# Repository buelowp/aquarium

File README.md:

# Aquarium Sensor Monitor

I have had aquariums for a while, so I decided one day to add some specific sensors to help me keep track of the
health of the aquarium over time. Atlas makes some really nice, if not expensive, water sensors than can be used in both
fresh and saltwater tanks. For my freshwater tank, I plan to add dissolved oxygen and a pH sensor to help me keep track
of what's going on during the day. I also plan to add a temperature monitor and have added support for keeping track 
of the flow rate for the pump and a water level sensor to make sure I have water in there. The goal is to give me 
some insight into tank health as time goes by, and provide me with rapid warning if something critically bad happens.

To do this, I've created a board to hold a Rasperry PI Zero W, along with space to add the Atlas sensors and a ADC to 
help me keep track of water level. It is a somewhat complicated 4 layer PCB that includes the PI, three Atlas sensor installations, two temp probes, a couple of random GPIO (to control whatever), and an 8 channel ADC, though currently 
I only use 1. They don't make a through hole 1 channel ADC that I can find.

This is also designed to work with my Android Things Aquarium display, which will give me some visual feedback when 
wanted about the state of the tank. It will also give me the ability to track cleanings, filter changes, and a list 
of other things that should be tracked over time to avoid letting them go too long.

## Installation

You need a PI zero, with build-essentials and cmake. You compile it doing the following

```
mkdir build
cd build
cmake ..
make
cp app/aquarium /usr/bin
```

You must copy the aquarium.config file to /root/.config, as this app MUST run as root. It's easiest if you start 
it from rc.local as the last item in the list. It has a function to wait on the network, so that shouldn't be too 
big a problem. If the MQTT server doesn't come up in 5 minutes, it will fail. The whole point of this is MQTT 
access to data. It also can talk to AdafruitIO, but doesn't block waiting for that. If that doesn't connect, then 
you can't talk to AdafruitIO.

I won't got into detail about how to build out the hardware right now.

## Configuration

I will describe how to populate the config file here soon.

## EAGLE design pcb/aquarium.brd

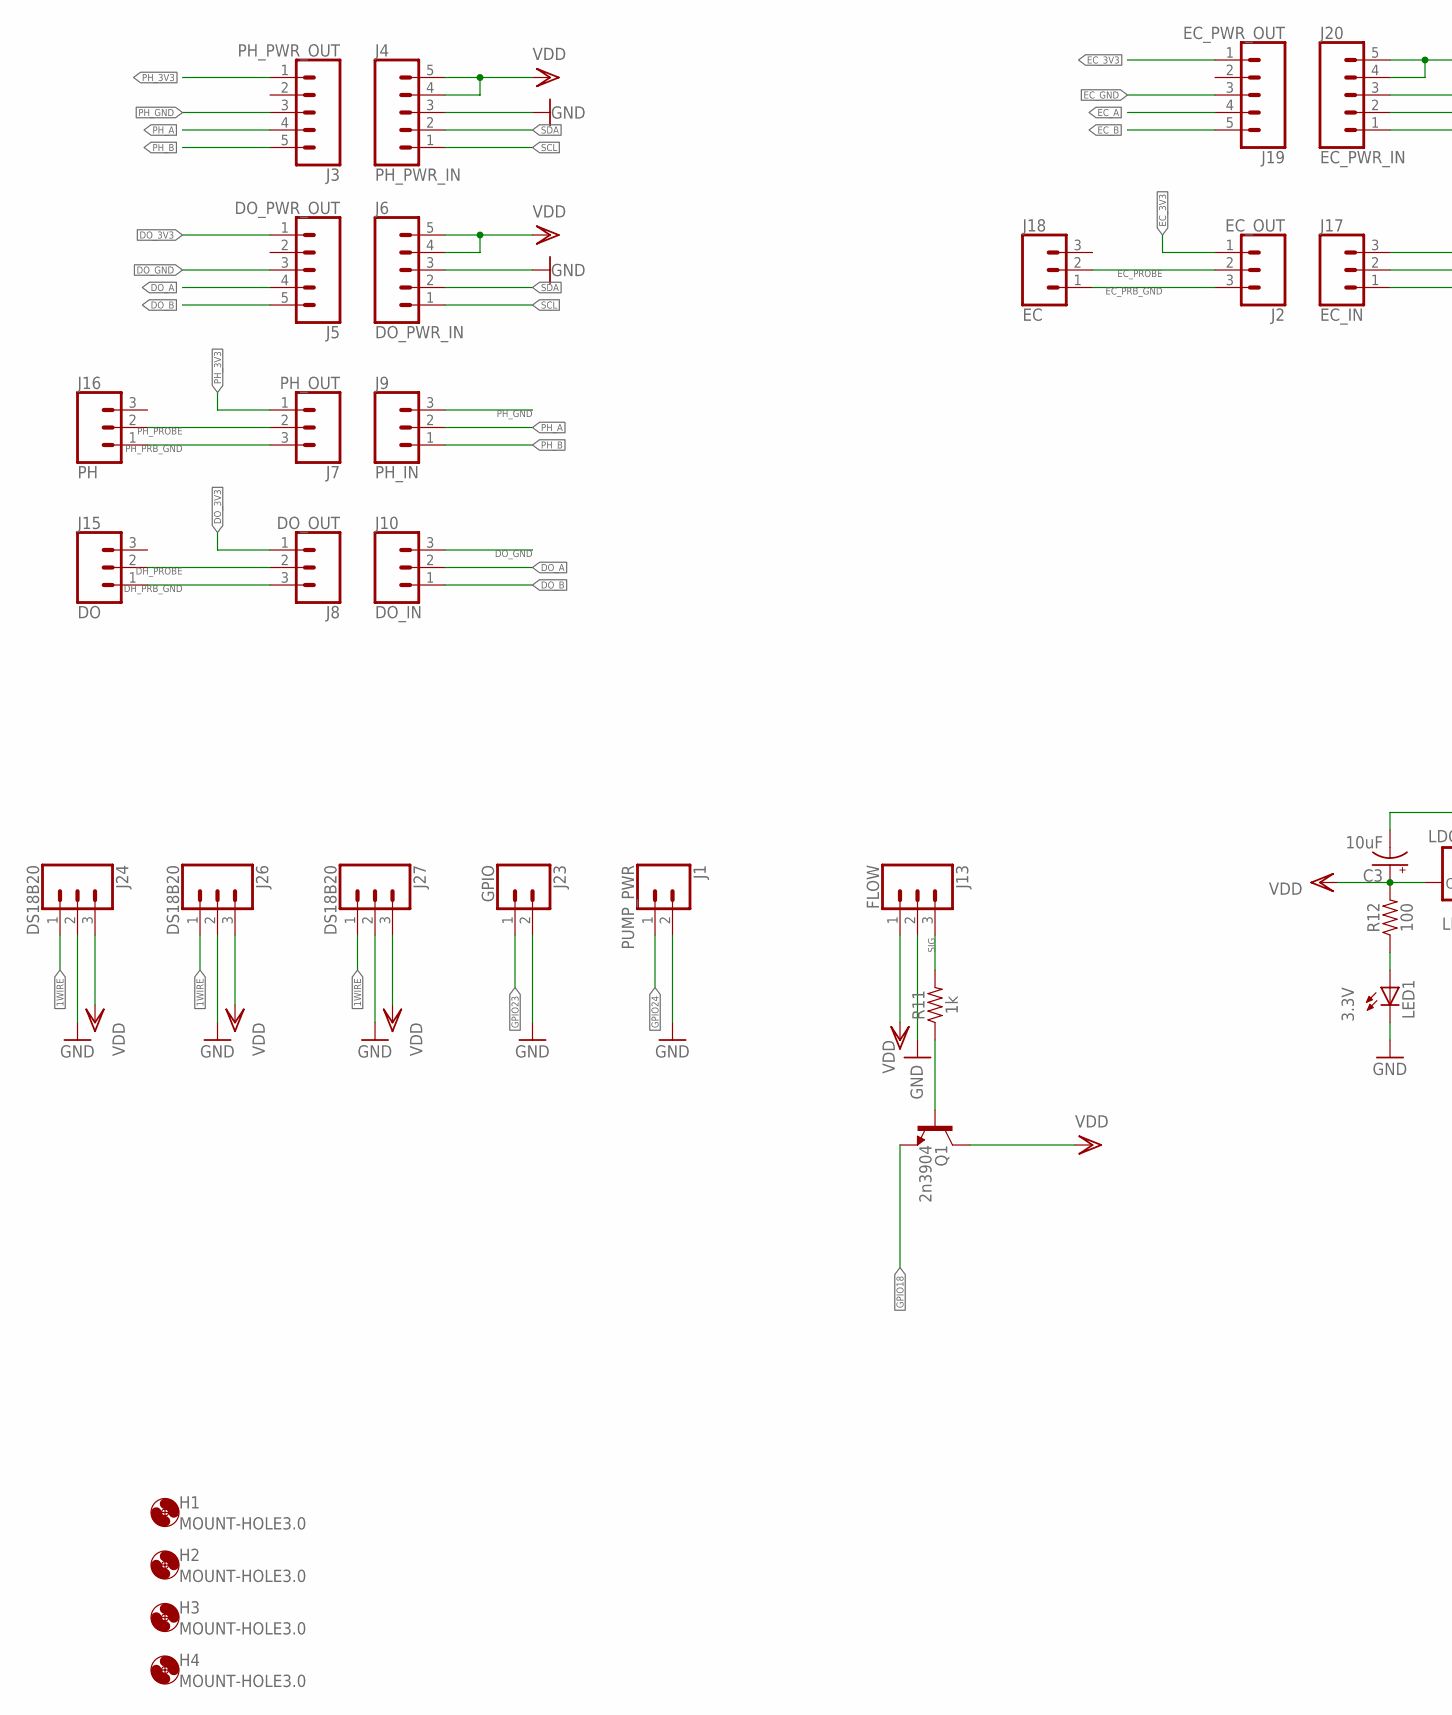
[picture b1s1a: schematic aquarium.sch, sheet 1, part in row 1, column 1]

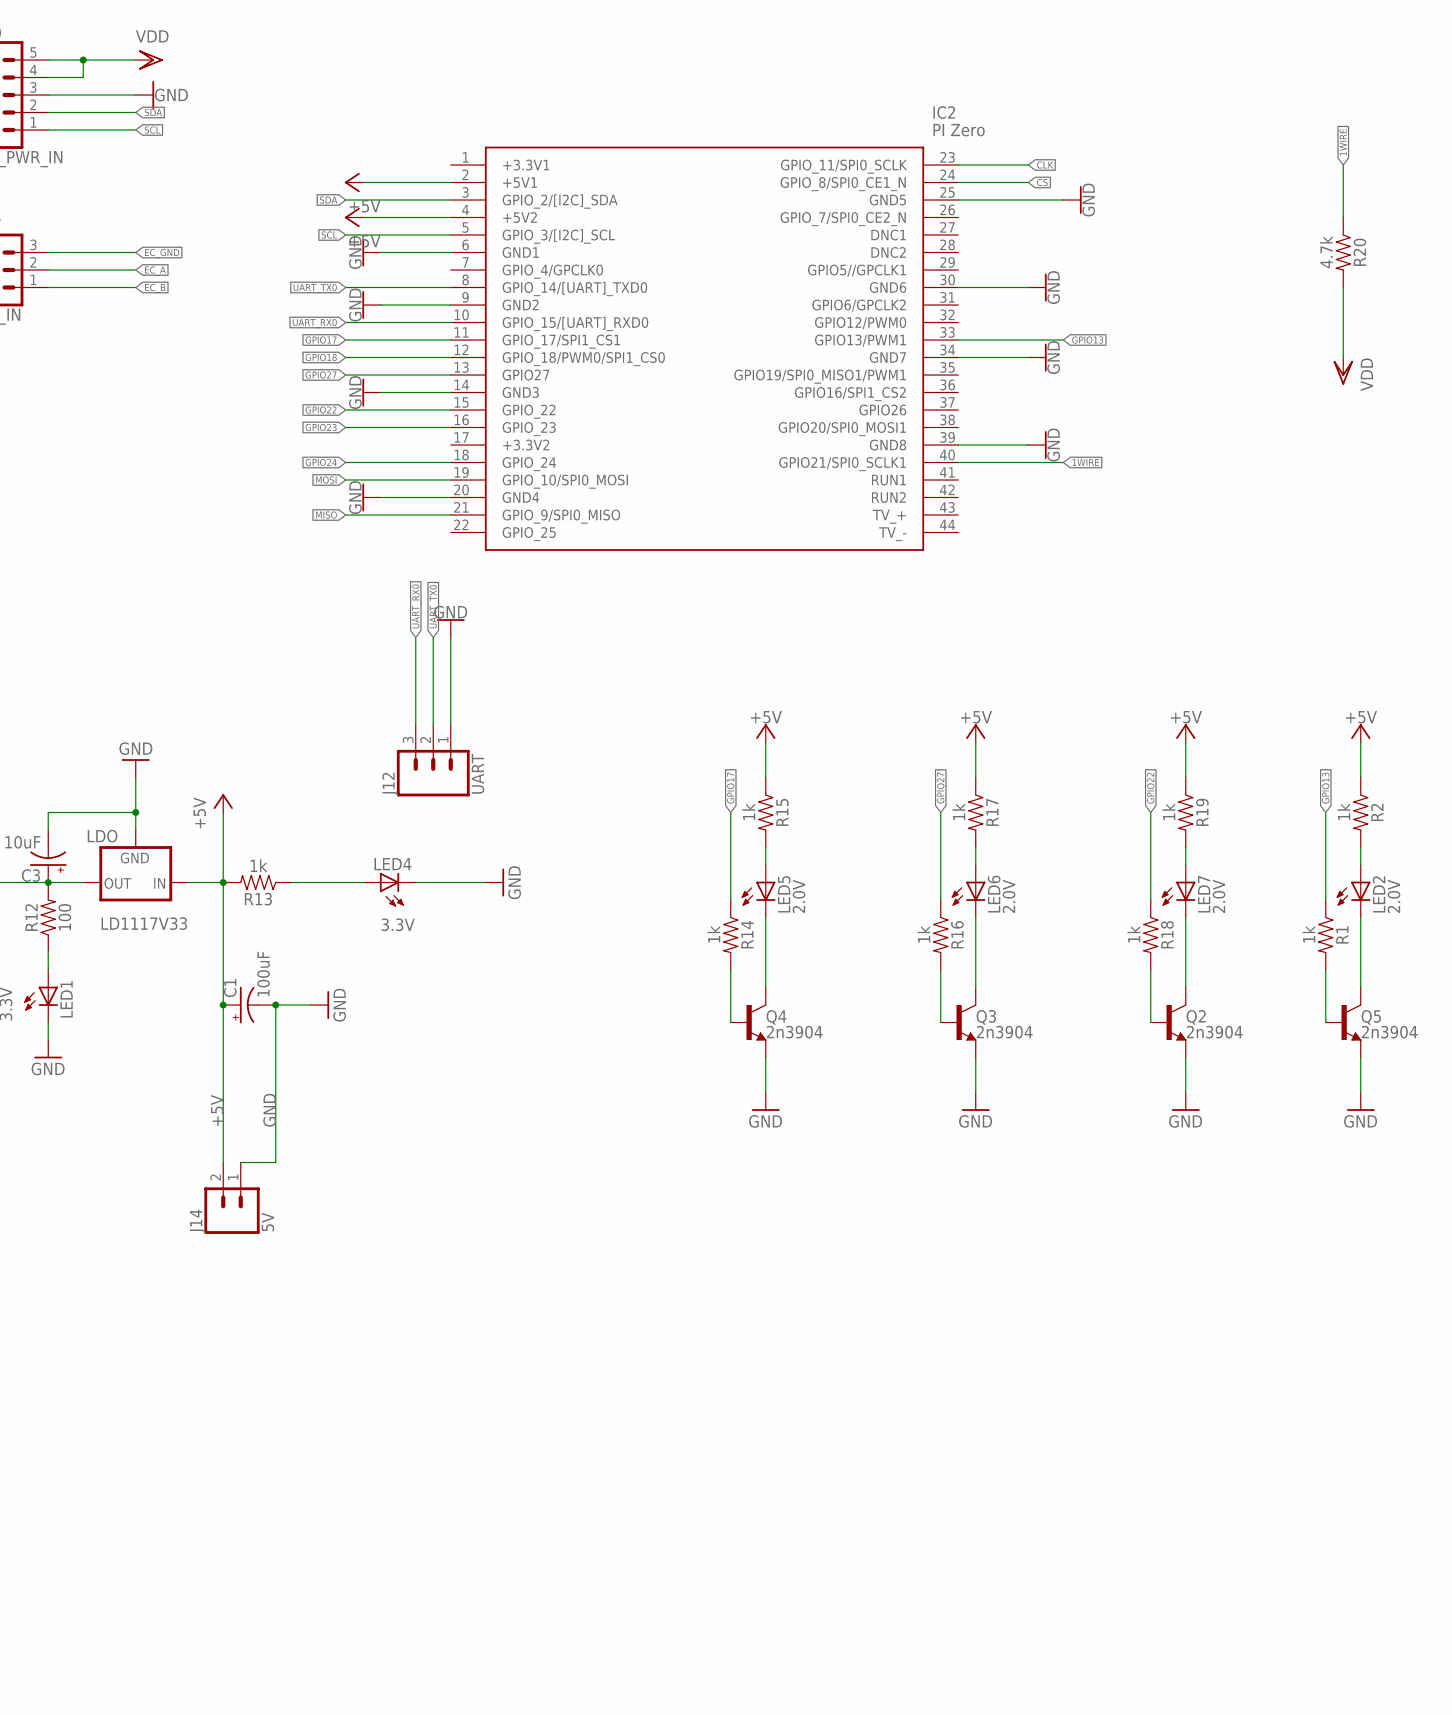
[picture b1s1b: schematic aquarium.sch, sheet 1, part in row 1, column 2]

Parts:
C1: 100uF; CPOL-RADIAL-2.5MM-6.5MM
C3: 10uF; CPOL-RADIAL-2.5MM-5MM
H1, H2, H3, H4: MOUNT-HOLE3.0; 3,0
IC2: PI Zero; RASPBERRYPIZEROWV13
J1: PUMP_PWR; 1X02
J2: EC_OUT; 1X03
J3: PH_PWR_OUT; 1X05
J4: PH_PWR_IN; 1X05
J5: DO_PWR_OUT; 1X05
J6: DO_PWR_IN; 1X05
J7: PH_OUT; 1X03
J8: DO_OUT; 1X03
J9: PH_IN; 1X03
J10: DO_IN; 1X03
J12: UART; 1X03
J13: FLOW; 1X03
J14: 5V; 1X02
J15: DO; 1X03
J16: PH; 1X03
J17: EC_IN; 1X03
J18: EC; 1X03
J19: EC_PWR_OUT; 1X05
J20: EC_PWR_IN; 1X05
J23: GPIO; 1X02
J24, J26, J27: DS18B20; 1X03
LDO: LD1117V33; 78XXL
LED1, LED4: 3.3V; LED3MM
LED2, LED5, LED6, LED7: 2.0V; LED3MM
Q1, Q2, Q3, Q4, Q5: 2n3904; TO-92
R1, R2, R11, R13, R14, R15, R16, R17, R18, R19: 1k; AXIAL-0.3
R12: 100; AXIAL-0.3
R20: 4.7k; AXIAL-0.3

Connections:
1WIRE: IC2.40 (GPIO21/SPI0_SCLK1), J24.1, J26.1, J27.1, R20.P$1 (1)
+5V: C1.1 (+), IC2.2 (+5V1), IC2.4 (+5V2), J14.2, LDO.OUT (IN), R2.P$1 (1), R13.P$2 (2), R15.P$1 (1), R17.P$1 (1), R19.P$1 (1); also elsewhere on the board
CLK: IC2.23 (GPIO_11/SPI0_SCLK); also elsewhere on the board
CS: IC2.24 (GPIO_8/SPI0_CE1_N); also elsewhere on the board
DH_PRB_GND: J8.3, J15.1
DH_PROBE: J8.2, J15.2
DO_3V3: J5.1, J8.1
DO_A: J5.4, J10.2
DO_B: J5.5, J10.1
DO_GND: J5.3, J10.3
EC_3V3: J2.1, J19.1
EC_A: J17.2, J19.4
EC_B: J17.1, J19.5
EC_GND: J17.3, J19.3
EC_PRB_GND: J2.3, J18.1
EC_PROBE: J2.2, J18.2
GND: C1.2 (-), C3.2 (-), IC2.6 (GND1), IC2.9 (GND2), IC2.14 (GND3), IC2.20 (GND4), IC2.25 (GND5), IC2.30 (GND6), IC2.34 (GND7), IC2.39 (GND8), J1.2, J4.3, J6.3, J12.1, J13.2, J14.1, J20.3, J23.2, J24.2, J26.2, J27.2, LDO.IN (GND), LED1.K (C), LED4.K (C), Q2.1 (E), Q3.1 (E), Q4.1 (E), Q5.1 (E); also elsewhere on the board
GPIO13: IC2.33 (GPIO13/PWM1), R1.P$1 (1)
GPIO17: IC2.11 (GPIO_17/SPI1_CS1), R14.P$1 (1)
GPIO18: IC2.12 (GPIO_18/PWM0/SPI1_CS0), Q1.1 (E)
GPIO22: IC2.15 (GPIO_22), R18.P$1 (1)
GPIO23: IC2.16 (GPIO_23), J23.1
GPIO24: IC2.18 (GPIO_24), J1.1
GPIO27: IC2.13 (GPIO27), R16.P$1 (1)
MISO: IC2.21 (GPIO_9/SPI0_MISO); also elsewhere on the board
MOSI: IC2.19 (GPIO_10/SPI0_MOSI); also elsewhere on the board
unnamed: LED1.A, R12.P$1 (1)
unnamed: Q1.2 (B), R11.P$1 (1)
unnamed: Q4.2 (B), R14.P$2 (2)
unnamed: LED4.A, R13.P$1 (1)
unnamed: Q3.2 (B), R16.P$2 (2)
unnamed: LED5.A, R15.P$2 (2)
unnamed: Q2.2 (B), R18.P$2 (2)
unnamed: LED5.K (C), Q4.3 (C)
unnamed: LED6.A, R17.P$2 (2)
unnamed: LED6.K (C), Q3.3 (C)
unnamed: LED7.A, R19.P$2 (2)
unnamed: LED7.K (C), Q2.3 (C)
unnamed: Q5.2 (B), R1.P$2 (2)
unnamed: LED2.A, R2.P$2 (2)
unnamed: LED2.K (C), Q5.3 (C)
PH_3V3: J3.1, J7.1
PH_A: J3.4, J9.2
PH_B: J3.5, J9.1
PH_GND: J3.3, J9.3
PH_PRB_GND: J7.3, J16.1
PH_PROBE: J7.2, J16.2
SCL: IC2.5 (GPIO_3/[I2C]_SCL), J4.1, J6.1, J20.1; also elsewhere on the board
SDA: IC2.3 (GPIO_2/[I2C]_SDA), J4.2, J6.2, J20.2; also elsewhere on the board
SIG: J13.3, R11.P$2 (2)
UART_RX0: IC2.10 (GPIO_15/[UART]_RXD0), J12.3
UART_TX0: IC2.8 (GPIO_14/[UART]_TXD0), J12.2
VDD: C3.1 (+), J4.4, J4.5, J6.4, J6.5, J13.1, J20.4, J20.5, J24.3, J26.3, J27.3, LDO.GND (OUT), Q1.3 (C), R12.P$2 (2), R20.P$2 (2); also elsewhere on the board

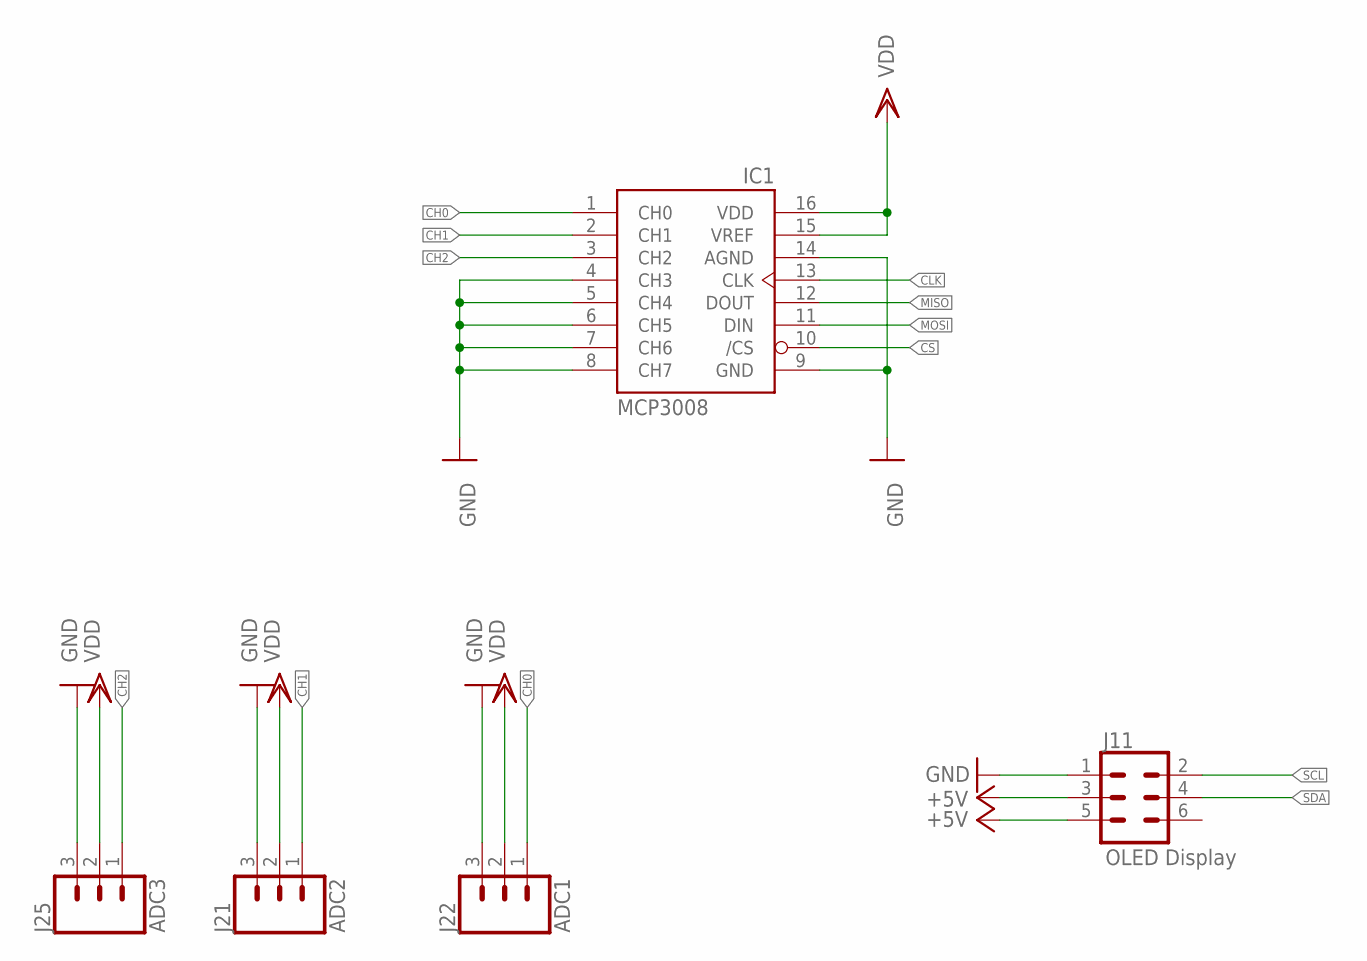
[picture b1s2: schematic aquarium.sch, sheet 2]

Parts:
IC1: MCP3008; DIL16
J11: OLED Display; 2X3
J21: ADC2; 1X03
J22: ADC1; 1X03
J25: ADC3; 1X03

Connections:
+5V: J11.3, J11.5; also elsewhere on the board
CH0: IC1.1 (CH0), J22.1
CH1: IC1.2 (CH1), J21.1
CH2: IC1.3 (CH2), J25.1
CLK: IC1.13 (CLK); also elsewhere on the board
CS: IC1.10 (/CS); also elsewhere on the board
GND: IC1.4 (CH3), IC1.5 (CH4), IC1.6 (CH5), IC1.7 (CH6), IC1.8 (CH7), IC1.9 (GND), IC1.14 (AGND), J11.1, J21.3, J22.3, J25.3; also elsewhere on the board
MISO: IC1.12 (DOUT); also elsewhere on the board
MOSI: IC1.11 (DIN); also elsewhere on the board
SCL: J11.2; also elsewhere on the board
SDA: J11.4; also elsewhere on the board
VDD: IC1.15 (VREF), IC1.16 (VDD), J21.2, J22.2, J25.2; also elsewhere on the board

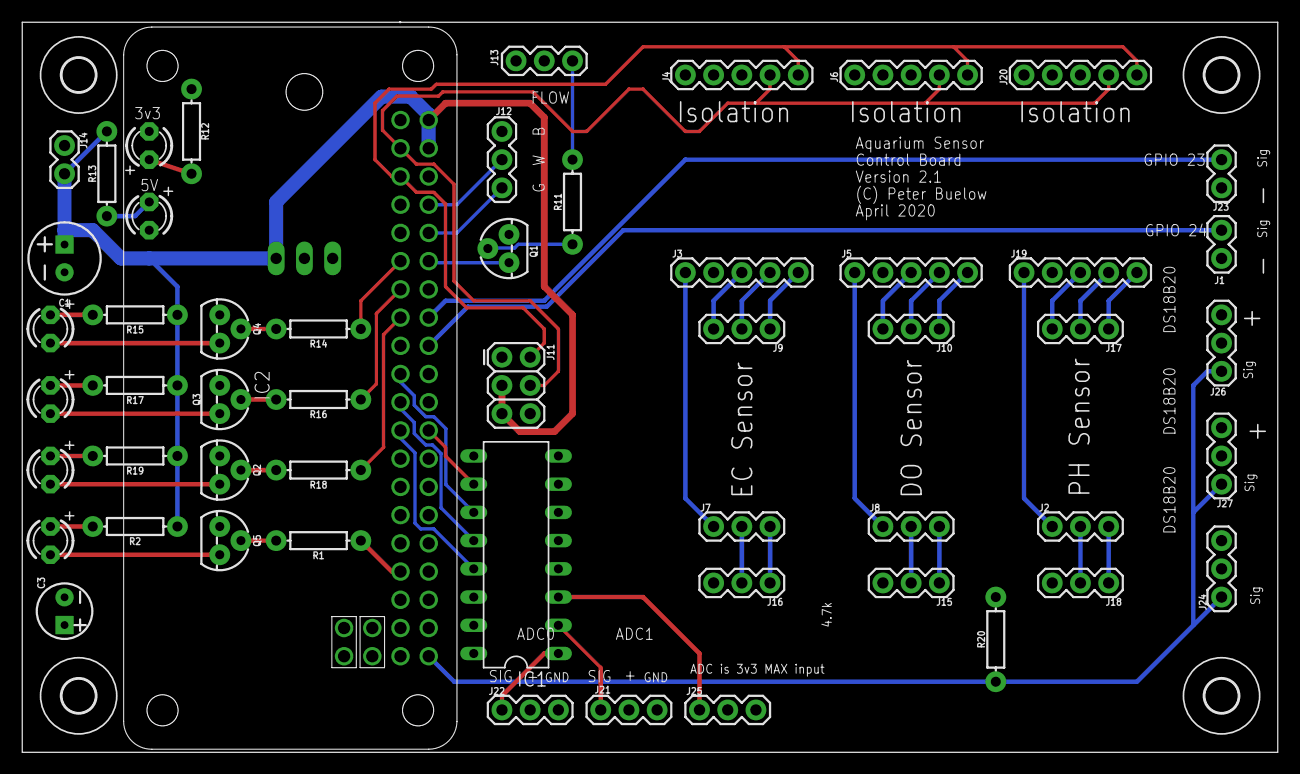
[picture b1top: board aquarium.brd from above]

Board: 4 copper layers, 113.0 x 65.7 mm, 59 parts (1 on the bottom side), 56 nets.

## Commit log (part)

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2019-08-28 Adding documentation
2019-08-29 Removing boost
    * Added a simple interval timer class
    * Updated i2c code to use new timer
2019-08-30 Fixups
    * Lots of API updates/changes/fixes
    * Fixed scoping of the Atlas parent/child classes
    * Fixed GpioInterrupt API issues and use newest version of GpioInterrupt
    * Got it to compile cleanly
2019-09-03 Fixing config file issues
    * Made path fixed for $HOME and ~
    * Added some error output
    * Fixed issue with creating config_t as a pointer
2019-10-03 Fixups
    * Adding some more logical config setup
    * Cleanup logging of config at startup
    * Cleanup config defaults to be less redundant
    * Allow for disabling of MQTT and AIO services
2019-10-04 Lots of work
    * Fixed issues with sensor base class to correctly do what it needs to
    do
    * Testing itimer, no real changes
    * Logging changes across the board
    * Now it can talk to the Atlas Science sensors correctly
2019-10-07 Getting closer
    * Fixups for making AS sensors work smarter
    * Added new AS sensor commands for both pH and DO
    * Got temperature via DS18B20 working
    * Lots of code cleanup
2019-10-08 Getting temperature working
    * Fixed up JSON for temp MQTT
    * Updated to new interface
2019-11-09 Fixes and updates
    * Added Green and Red LED for notifications
    * Bug fixes
    * Addition of flow sensor handling
2019-11-10 More work to fix issues
    * Updated config file for more options
    * Fixed some issues with program
    * Updated temperature to do the right thing
    * Some debug additions
2019-11-10 Logging changes
    * Changed the JSON for temperature
    * Continue to work on status bug
    * Fixed syslog entries
2019-11-11 Fixups
    * Fixing an issue with strings from the AS devices, they needed cleaning
    * Some logging cleanups
    * Added a DO calibration routine, not tested
    * Added JSON handler to avoid doing it manually
2019-11-13 Adding PCB files for safe keeping
2019-11-16 Bumping some things
    * Minor updates to main
    * Fixing PCB and schematic
2019-11-17 First pass at using state leds
2019-12-27 Checkpoint
    * Adding reading for PH
    * Fixed timeout for reading command
    * Make it possible to get last reading
2019-12-27 Big changes
    * Restructure directories
    * Add a new calibration application
2019-12-27 Checkpoint
    * calibration is starting to work
2019-12-27 More calibration work
    * Couldn't get condition variables to work, switched to raw mutex
    * Some display cleanup
2019-12-28 Fixes
    * Made it mostly work, still needs some testing
2019-12-28 Lots of fixes
    * Added LED support and fixed a LED enable bug
    * Added a query and clear command to the list of options
    * Fixed a bug which stored the last ph value as an int
    * Added some prints
2019-12-28 Fix missing usage details
2019-12-29 Some updates
    * Once a minute, just collect all the results and then send it if we need to
    * Get PH data every 10 seconds now
    * Disable some of the other timers until we need them
2019-12-29 Useability updates
    * Fixed printing to be easier to understand
    * Remove timers that are no longer necessary
    * Add a DO value retriever
    * Make the read command time delay configurable
2019-12-29 Creating a calibration routine for the dissolved oxygen probe
2019-12-29 Temp compensation additions
    * Fixed the Temperature class to use doubles
    * Added new temp compensation methods
    * Query temp compensation at startup
    * Set the temp compensation at startup and after 15 minutes
2019-12-30 More fixes and work
    * Added a new temp compensation print and decode
    * Allow analog resolution to be set by config
    * If MQTT is enabled, publish the data
    * There is a bug in setWarning Display for the temp function, it will segfault still
2019-12-30 Updating PCB design to latest
2019-12-31 Fixing issues with setting temperature compensation
    * Changed the callbacks
    * Fixed a bug in DO class
    * Fixed a print bug which made it looks like two pH returns
2019-12-31 Updates to the PCB
    * Removed the power jack and replaced with a 2 wire solution
    * Routing changes associated with the jack removal
    * Added a new Analog channel to round out 4
    * Moved some of the GPIO pins around
2019-12-31 Simple fixes
    * Add time to the MQTT JSON payload
    * Make the system calibrate temp compensation once an hour
2020-01-02 Lots of updates
    * Added a new MCP3008 handler, removed the MCP3424 handler
    * Created a new configuration singleton to handle app config data
    * Fixups to cmake files to build
    * Remove all references to the MCP3424
    * Some function reordering
2020-01-02 Add missing files
2020-01-11 Setup AIO updates for individual stats
2020-01-11 Adding better DS18B20 handling
    * Add a new handler class for all DS18B20 devices
    * Fixup the actual device class to be smarter
2020-01-12 Build fixes mostly
2020-01-12 Some simple changes before I move to the pi
2020-01-14 Fixes
2020-01-14 Fixing a few things
    * Temperature name is now correct for all cases
    * Print JSON for now
2020-01-14 Fixing some issues
    * Make sure the MQTT client knows it's connected
    * Actually check for connection correctly
2020-02-10 Fixups
    * Added DO back in
    * Fixed how we do time strings for JSONwq
2020-02-10 Chaning timer code to try to make it more accurate
2020-02-10 Adding a debug print to make sure it works
2020-02-10 Using nanosleep with some corrections
2020-02-10 Reverting and fixing a few things
    * Going back to sleep_for
    * Make interval the time value
    * try/catch on the function in the interval timer
2020-02-21 Updating mcp3008 to use wiringPi
2020-02-23 More work towards a real error state handler
2020-02-23 Continuing work on error handling
    * Pry won't compile yet, but continuing on
2020-02-24 More work on an error management routine
2020-02-24 Cleanups
    * Fix some issues in the error handler
    * Make timers sleep a little less than total time when north of a minute
2020-02-25 Adding some messaging context so we can store the data
2020-02-25 Making it possible to have many DS18B20 devices
2020-02-25 Cleaning up DS18B20 temp readings
    * Having 2 classes do the same thing was confusing, so I reduced it to 1
2020-02-25 More cleanups
2020-02-26 Got it compiliing
    * Fixups to dependencies
    * Moved ErrorHandler class out of configuration to avoid circular dependency
    * Fixed up Temp API usage
2020-02-26 Some quick changes
2020-02-26 Quick fixup for error handling
2020-02-26 Forgot to turn off the green led
2020-02-26 Some updates for better network checking
2020-02-27 Some fixups
    * Fixed a bug which would cause sending result data to never work
    * Added a flow rate enable option in the config to disable the flow rate calcs if a device isn't present
2020-02-28 Fixes and updates to work correctly
2020-02-28 Got it working
    * Fixed timing by testing iTimer offsets on the RPi
    * Fixed issues with iterators in main
2020-02-28 Fixing a bug where the warning wouldn't clear correctly
2020-03-02 Update README.md
    Add some content
2020-03-10 Issue #4: Beginning of the changes to support paho
    * Implement the new client callback handlers
    * Migrate from mosquitto to paho publish (some, not all)
    * Migrate errors to use paho now
    * Updates to the build system to support new MQTT
2020-03-11 Issue #4: Build fixes, should build now for testing
2020-03-12 Issue #4: Fixing a build issue
2020-03-12 Fixups
    * Fixed timer to be more accurate for more than 1 minute intervals
    * Removed the network check, the MQTT setup should be the check
2020-03-13 Quick changes to remove the net test, it wasn't working
2020-03-13 Issue #3: Got initial work on being able to store probe names
    * Added configuration functionality
    * Added messaging
    * Cleaned up some naming and variables in configuration
2020-03-13 Issue #3: Do the temp device array more correctly now
2020-03-15 Making sure we can create the config entry if it doesn't exist
2020-03-15 Fixing some issues with config parsing
2020-03-15 Mostly working now
    * Can add to array
    * Can add a new array
    * Can change array element values by key
    * Still a problem with adding a new array entry if an array already exists
2020-03-15 Adding a TODO to help me remember to fix this
2020-03-15 Allow for creating new entries if new temp devices found
2020-03-15 Fixing a function name bug
2020-03-15 Turn of the RPi nlohmann c++ note
2020-03-15 First pass at a block on main until mqtt connects
2020-03-15 Fix a bug in reporting available temp devices
2020-03-15 Add some incoming message debug and fix up the temp probe reporting a bit
2020-03-16 Got mqtt sync working
2020-03-17 Finally got it
    * Can update a temp device using MQTT
2020-03-17 Make it possible to read device name
2020-03-18 Changing the temp directory name
2020-03-22 Added PAHO non SSL Adafruit IO connection
    * Untested, but should work
    * Not wired up to send data to AIO yet.
2020-03-23 Bump some of the AIO connection details to be better fit into this design.
2020-03-25 Fixing a missing CXX_FLAGS option for cmake
2020-03-26 Lots of work to get AIO connections going
    * Added support for secure and insecure
    * Fixed up how we start our MQTT connections
    * Fixed some bugs in the configuration itself
2020-03-27 Fixing bug in MQTT work
    * If you don't create the callback in a way that lives outside the function, this fails pretty badly
2020-03-27 Fixups for more scoping issues
    * Make the connection options a class member, same as the SSL options
2020-03-27 Send AIO data completely now
2020-03-27 Issue #7: Complete AIO compatibility
2020-03-27 Issue #11: Fixing the naming problem in MQTT
2020-03-27 Removed a lot of old dead code
    * Removed all references to gpio interrupt, and replaced with wiringPi
    * Cleaned up and removed the flow rate stuff, will revisit in the future
    * Added a common functions file
2020-03-28 Fixing a conflict with wiringPi
    * Turns out wiringPi defines both LOW and HIGH, so I had to rename mine even though it's in a namespace
2020-03-28 Issue #13: Forgot to add this setup
2020-04-21 Working backwards to get this building again
2020-04-21 Got it buliding finally
2020-04-21 Cleanups for Issue #13
2020-04-22 Issue #15: Adding the ability to get rapid water level measurements
    * Make it so the timer can be managed anywhere
    * Add new MQTT messaging to turn on and off fast waterlevel messages
2020-04-22 Issue #16: Add ability to turn off LEDs
    * Set LEDS off via the Atlas API
2020-08-31 More fixes and updates
    * Beginnings of a time remaining in millis for timers
    * Fixed some build issues where I clobbered CXX_FLAGS accidentally
2020-08-31 More work on errors
    * Fixup ErrorHandler to be a bit more flexible
    * Added some errors into main
    * Added some more doxygen documentation
2020-09-03 More work getting this going
    * More error handling fixuups
    * Improve the MQTT callbacks I think. This should make them less complicated.
    * Remove the old MQTT directory, we aren't using it anymore.
    * Working main, still have an error in the timers I think.
2020-09-05 Too many changes to document well
    * Switched from mqtt::message_ptr to just putting the message into the publish(), this may have created a memory leak though
    * Fixed up a lot of printing issues
    * Lots of cmake changes for debug additions
2020-09-06 Fixing missing header file
2020-09-06 Printing fixups, and a small change to how I store the callbacks for the MQTT setup
2020-09-09 Updating the board to the latest
2020-09-09 Fixups and new functions
    * Added monitoring for GPIO pins, this is a read only right now, will need to add type later
    * Fixed some prints
    * Take out the spi device, this is handled internally by wiringPi

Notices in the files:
parts and their libraries:
SparkFun-Capacitors: Licensing: Creative Commons ShareAlike 4.0 International - https://creativecommons.org/licenses/by-sa/4.0
